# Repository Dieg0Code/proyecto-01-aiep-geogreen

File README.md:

# GeoGreen Escolar

GeoGreen comenzó como una propuesta para monitorear el llenado de contenedores de
reciclaje y evolucionó hacia un programa educativo de AIEP Osorno. El dispositivo
funciona como caso central para enseñar sostenibilidad, sensores, datos,
prototipado, desarrollo agéntico y comunicación de soluciones.

- **Socio comunitario:** Instituto Comercial Liceo Bicentenario, Osorno.
- **Público objetivo:** cerca de 60 estudiantes, organizados en equipos.
- **Programa:** tres talleres, cuatro mentorías, ensayo y competencia final.
- **Lógica tecnológica:** `sensar → enviar → visualizar → alertar`.

## Estado vigente · julio de 2026

El repositorio reúne dos líneas de trabajo conectadas:

1. **El dispositivo:** firmware, simulación, prototipos físicos, visualización,
   diseño 3D y PCB.
2. **El programa educativo:** talleres, cronograma, presentaciones, infografías,
   banco de ideas, inventario y materiales para la competencia.

Los Talleres 1 y 2 cuentan con planificación y presentación. El Taller 3 dispone
de un paquete completo de 90 minutos: README pedagógico, deck editable, banco
audiovisual, podcast de coordinación y una serie de cuatro infografías.

El calendario operativo vigente está centralizado en
[`cronograma/README.md`](cronograma/README.md). Los talleres se realizarán el 17,
18 y 24 de agosto; las mentorías se extenderán hasta el 28 de septiembre; el
evento final con jurado y premiación está programado para el 5 de octubre; y el
cierre interno corresponde a la semana del 12 de octubre.

## Evolución del dispositivo

GeoGreen no corresponde a un único circuito inmutable. El repositorio conserva
distintas versiones porque cada una responde a una etapa del proceso.

| Versión o track | Propósito | Estado |
|---|---|---|
| Prototipo original de referencia | `HC-SR04` + módulo de comunicación celular. No incluía semáforo ni buzzer. | Antecedente histórico reconstruido para explicar la evolución. |
| `arduino/` | Firmware base con porcentaje, semáforo y buzzer; simulación y pruebas con PlatformIO + Wokwi CLI. | Implementado y automatizado. |
| `arduino-r4/` | Prototipo físico con UNO R4 WiFi, `HC-SR04`, OLED, semáforo y buzzer; además, demos en la matriz LED integrada. | Construido y probado en protoboard. |
| `geogreen-v0/` | Validación de medición con ESP32 DevKit + sensor ultrasónico impermeable `A02YYUW`. | Track experimental de medición. |
| `geogreen-v1/` | PCB interna de dos capas con ESP32-C6, USB-C, conectores, semáforo y buzzer. | Candidata de diseño con DRC limpio; requiere revisión de ingeniería antes de fabricar. |
| `app/` | PWA con mapa de Osorno, estados, historial, batería, señal y alertas. | Interfaz funcional sobre una capa de telemetría reemplazable. |
| `web/` | Contenedor 3D interactivo y plano explosionado del módulo. | Demos funcionales sin proceso de build. |

La versión física educativa utilizada como demostración transforma una medición
de distancia en una respuesta comprensible:

1. El `HC-SR04` mide la distancia entre la tapa y el contenido.
2. La placa calcula un porcentaje de llenado.
3. El semáforo utiliza los umbrales `< 40 %`, `40–79 %` y `≥ 80 %`.
4. La OLED muestra porcentaje y estado.
5. El buzzer se activa en el estado rojo.
6. Una versión conectada puede enviar el dato para visualizarlo y generar alertas.

## Programa educativo y competencia

| Etapa | Fecha | Propósito |
|---|---|---|
| Taller 1 | Lunes 17 de agosto | Identificar un problema ambiental concreto y formar los equipos. |
| Taller 2 | Martes 18 de agosto | Comprender residuos, materiales, separación y reciclabilidad. |
| Taller 3 | Lunes 24 de agosto | Relacionar el problema con una variable, un sensor y una primera prueba segura. |
| Mentorías 1–4 | 31 de agosto al 28 de septiembre | Revisar avances, orientar decisiones y destrabar dificultades. |
| Evento final | Lunes 5 de octubre | Presentar ante el jurado, recibir retroalimentación y participar en la premiación. |

El desarrollo de las propuestas ocurre principalmente mediante el trabajo
autónomo de cada equipo entre sesiones. Las mentorías no sustituyen ese trabajo:
sirven para revisar evidencia, orientar y ayudar a resolver bloqueos concretos.

GeoGreen muestra hasta dónde puede crecer una idea, pero no es una solución que
los equipos deban copiar. La competencia valora la relación entre problema,
sensor, respuesta, evidencia, mejora y claridad de la presentación.

Los lineamientos comunes de participación, presentación, jurado, evaluación,
desempate y seguridad se encuentran en
[`concurso/README.md`](concurso/README.md). La versión institucional para
distribución está disponible en
[`concurso/documentos/lineamientos-concurso-final-geogreen.pdf`](concurso/documentos/lineamientos-concurso-final-geogreen.pdf).

## Inicio rápido

### Simulación y pruebas del firmware base

Requiere PlatformIO, Wokwi CLI y un token de Wokwi guardado fuera del repositorio
en `~/.wokwi_token`.

```bash
bash arduino/sim.sh
bash arduino/test.sh
```

### Prototipo físico UNO R4 WiFi

```bash
pio run -d arduino-r4/geogreen_proto
pio run -d arduino-r4/geogreen_proto -t upload
```

### Aplicación de monitoreo

```bash
cd app
npm install
npm run dev
```

### Visualización 3D

```bash
python -m http.server 8099 --directory web
```

Abrir `http://localhost:8099/` para el contenedor o
`http://localhost:8099/plano.html` para el plano del módulo.

## Mapa del repositorio

```text
.
├── arduino/                 # Firmware base, Wokwi, pruebas, cableado y 3D
├── arduino-r4/              # Demos y prototipo físico UNO R4 WiFi
├── geogreen-v0/             # Validación ESP32 DevKit + A02YYUW
├── geogreen-v1/             # PCB interna con ESP32-C6
├── app/                     # PWA de monitoreo
├── web/                     # Contenedor 3D y plano interactivo
├── talleres/01-03/          # Paquetes pedagógicos de los talleres
├── banco-ideas/             # Ideas semilla y sensores seleccionados
├── concurso/                # Lineamientos y documentos del evento final
├── cronograma/              # Calendario operativo vigente
├── reuniones/               # Materiales y antecedentes de coordinación
├── docs/                    # Inventario, infografías, presupuestos y guías
└── tools/                   # Sistema de slides y validadores
```

Índice ampliado de materiales: [`MATERIALES.md`](MATERIALES.md).

## Seguridad eléctrica esencial

- La UNO R4 WiFi trabaja con lógica de `5 V`; el pin `Echo` del `HC-SR04` puede
  conectarse directamente.
- Un ESP32 DevKit trabaja normalmente con lógica de `3,3 V`; el mismo `Echo` de
  `5 V` requiere divisor de voltaje o adaptación de nivel.
- Todo circuito se arma y revisa desconectado. Antes de energizar se comprueban
  voltaje, pinout, polaridad, resistencias y posibles cortocircuitos.

## Fuentes documentales

- [`RESUMEN-PROYECTO.md`](RESUMEN-PROYECTO.md) — alcance formal de la postulación y
  diferencia respecto del calendario operativo.
- [`PLAN-GEOGREEN-ESCOLAR.md`](PLAN-GEOGREEN-ESCOLAR.md) — estado de ejecución y
  articulación del programa.
- [`cronograma/documentos/cronograma-vigente-2026.md`](cronograma/documentos/cronograma-vigente-2026.md)
  — fuente única de fechas operativas.
- [`talleres/03/README.md`](talleres/03/README.md) — fuente pedagógica del Taller 3.
- [`concurso/README.md`](concurso/README.md) — lineamientos del Concurso Final
  GeoGreen Escolar 2026.

---

Proyecto académico de Vinculación con el Medio · AIEP Osorno · Ingeniería,
Energía y Tecnología + Desarrollo Social y Educación.

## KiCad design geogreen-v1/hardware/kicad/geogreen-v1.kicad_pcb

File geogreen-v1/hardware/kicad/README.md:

# GeoGreen V1 — PCB fab candidate (KiCad)

Placa V1 candidata a fabricacion: ruteada en 2 capas, sin ratsnest, con reporte
DRC limpio en KiCad 10 (`0 DRC violations`, `0 unconnected pads`). Sigue siendo
necesaria una revision humana de BOM/MPN/datasheets antes de ordenar unidades.

La placa se genera por script con la API Python de **KiCad 10** (`pcbnew`) y el
logo de serigrafía se vectoriza con **OpenCV**. Todos los componentes usan
footprints y modelos 3D estándar de KiCad, salvo el ESP32-C6 que usa el STEP
oficial de Espressif (con color).

## Cómo regenerar (orden)

Desde cualquier directorio (los scripts anclan sus rutas a su propia carpeta):

```bash
KDIR=geogreen-v1/hardware/kicad

# 1. Modelo 3D oficial del ESP32-C6.
#    Ya vive en models/ESP32-C6-MINI-1.step para que el render sea reproducible.
#    Fuente original: github.com/espressif/kicad-libraries

# 2. Logo AIEP -> poligonos de serigrafia (brand/logo_silk.json).
uv run --with opencv-python-headless --with numpy python "$KDIR/brand/vectorize_logo.py"

# 3. Generar la placa .kicad_pcb.
"/c/Program Files/KiCad/10.0/bin/python.exe" "$KDIR/create_v1_product_board.py"

# 4. Autorutear pistas 45°/ortogonales con Freerouting headless.
"/c/Program Files/KiCad/10.0/bin/python.exe" "$KDIR/autoroute.py"

# 5. Validar DRC.
kicad-cli pcb drc "$KDIR/geogreen-v1.kicad_pcb" --output "$KDIR/exports/drc.rpt"
```

Requisitos:
- `models/ESP32-C6-MINI-1.step` debe existir (paso 1) — es el módulo real con color.
- `brand/logo_silk.json` lo produce el paso 2 desde `brand/logo-aiep-source.png`.
- El root de footprints de KiCad se resuelve por la variable `KICAD10_FOOTPRINT_DIR`
  (o `KICAD_FOOTPRINT_DIR`), con fallback a la ruta por defecto de Windows.
- `autoroute.py` espera Java 25 en Scoop (`temurin-lts-jdk`) y Freerouting en
  `~/.local/lib/freerouting.jar`. Se puede sobrescribir con `GEOGREEN_JAVA` y
  `GEOGREEN_FREEROUTING_JAR`.

## Render 3D

Render fotorrealista (raytracing) — **usar `--quality high`**, no el `basic` por
defecto (que se ve gris/mate):

```bash
kicad-cli pcb render -o exports/geogreen-v1-product-render.jpg \
  --quality high --floor --perspective --width 1920 --height 1200 \
  --rotate '-25,0,-25' --background opaque geogreen-v1.kicad_pcb
```

## Fabricacion

```bash
kicad-cli pcb export gerbers geogreen-v1.kicad_pcb \
  --output exports/fabrication \
  --layers F.Cu,B.Cu,F.Paste,B.Paste,F.SilkS,B.SilkS,F.Mask,B.Mask,Edge.Cuts \
  --subtract-soldermask --check-zones

kicad-cli pcb export drill geogreen-v1.kicad_pcb \
  --output exports/fabrication --format excellon --excellon-units mm \
  --excellon-separate-th --generate-map --generate-report \
  --report-path exports/fabrication/drill-report.rpt

kicad-cli pcb export pos geogreen-v1.kicad_pcb \
  --output exports/fabrication/geogreen-v1-pos.csv \
  --format csv --units mm --side both
```

## Notas de diseño

- **Sensor ultrasónico A02YYUW**: es externo, impermeable (IP67), conectado por
  **cable con conector PH2.0-4P** (JST PH, paso 2.0 mm, 4 pines: VCC/GND/TX/RX).
  En la PCB solo va el header JST-PH que aparea con ese cable; el sensor no va
  montado en la placa y no se muestra en el render.
- Los designadores de referencia se ocultan en el render limpio; el archivo PCB
  mantiene referencias internas y la posicion de componentes se exporta en CSV.
- Algunos valores siguen siendo funcionales/genericos (`PTC`, `3V3_REG`) hasta
  cerrar BOM/MPN. No ordenar ensamble sin revisar esos MPN.
- El script genera zonas GND con hueco bajo la antena, pero no llama
  `ZONE_FILLER.Fill()` desde Python: KiCad 10 en Windows puede hacer crash con
  el footprint real `ESP32-C6-MINI-1` y ese keep-out. El autoruteo exporta DSN
  sin zonas para enrutar GND como pistas reales; los Gerbers se exportan con
  `--check-zones`.

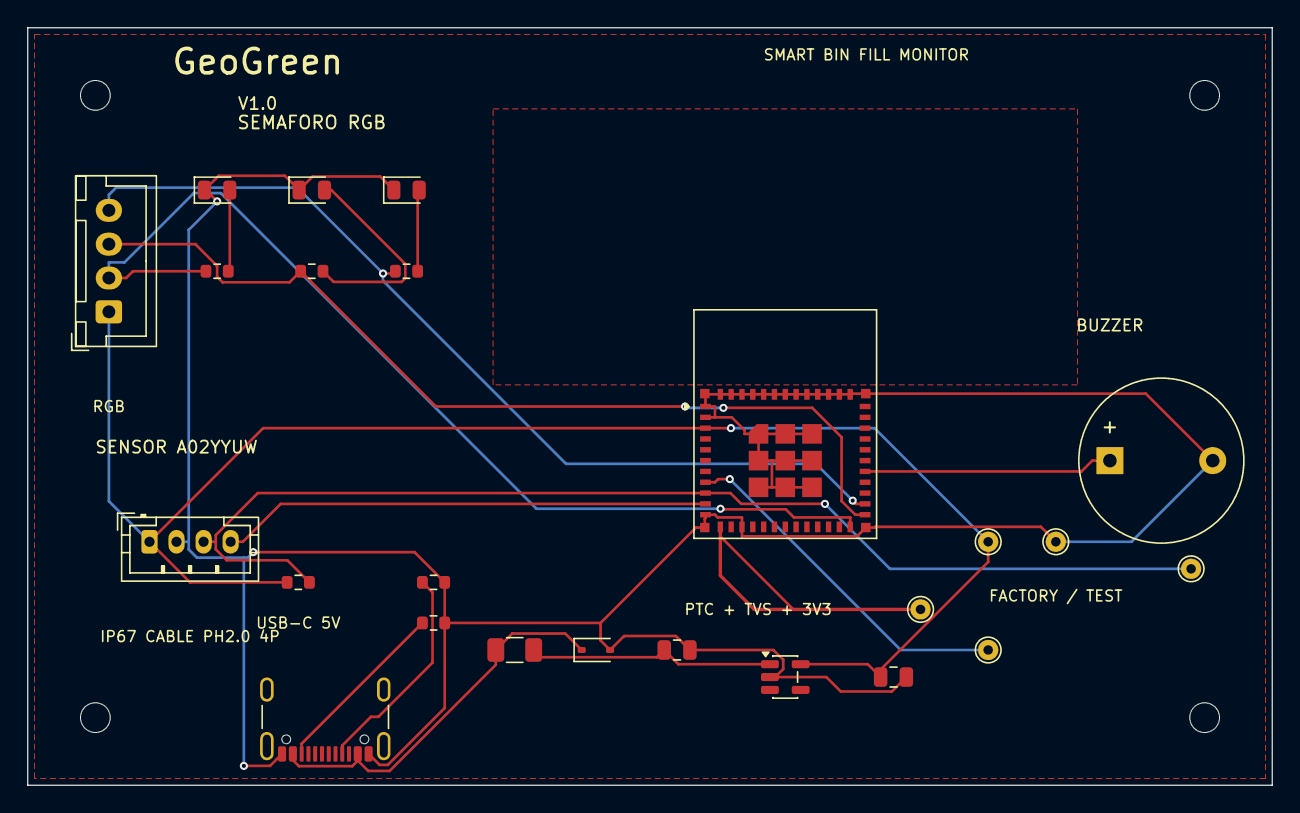
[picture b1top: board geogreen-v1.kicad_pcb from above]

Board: 2 copper layers, 92.0 x 56.0 mm, 28 parts (0 on the bottom side), 17 nets.

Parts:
BZ1: BUZZER; Buzzer_12x9.5RM7.6
C1, C2: 10uF; C_0805_2012Metric
D1: TVS; D_SOD-323
D2: LED_R; LED_0805_2012Metric
D3: LED_G; LED_0805_2012Metric
D4: LED_B; LED_0805_2012Metric
F1: PTC; Fuse_1206_3216Metric
H1, H2, H3, H4: M2; MountingHole_2.2mm_M2
J1: USB-C; USB_C_Receptacle_GCT_USB4105-xx-A_16P_TopMnt_Horizontal
J2: A02YYUW_PH2.0; JST_PH_B4B-PH-K_1x04_P2.00mm_Vertical
J4: RGB_SEMAFORO; JST_XH_B4B-XH-A_1x04_P2.50mm_Vertical
R1: CC1_5K1; R_0603_1608Metric
R2: CC2_5K1; R_0603_1608Metric
R3: SENSOR_RX_10K; R_0603_1608Metric
R4: LED_R_1K; R_0603_1608Metric
R5: LED_G_1K; R_0603_1608Metric
R6: LED_B_1K; R_0603_1608Metric
TP1: 3V3; TestPoint_THTPad_D1.5mm_Drill0.7mm
TP2: GND; TestPoint_THTPad_D1.5mm_Drill0.7mm
TP3: UART_RX; TestPoint_THTPad_D1.5mm_Drill0.7mm
TP4: EN; TestPoint_THTPad_D1.5mm_Drill0.7mm
TP5: BOOT; TestPoint_THTPad_D1.5mm_Drill0.7mm
U1: ESP32-C6-MINI-1
U2: 3V3_REG; SOT-23-5

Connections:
3V3: C2.1, J2.1, J4.1, R3.1, TP1.1, U1.3, U2.5
5V_PROTECTED: C1.1, F1.2, U2.1
BOOT_IO0: TP5.1, U1.12
BUZZER_OUT: BZ1.1, U1.29
EN: TP4.1, U1.8
GND: BZ1.2, C1.2, C2.2, D1.2, D2.1, D3.1, D4.1, J1.A1, J1.A12, J1.B1, J1.B12, J2.2, R1.2, R2.2, TP2.1, U1.1, U1.2, U1.11, U1.14, U1.36, U1.37, U1.38, U1.39, U1.40, U1.41, U1.42, U1.43, U1.44, U1.45, U1.46, U1.47, U1.48, U1.49, U1.50, U1.51, U1.52, U1.53, U2.2
LED_B: J4.4, R6.1, U1.26
LED_B_ANODE: D4.2, R6.2
LED_G: J4.3, R5.1, U1.25
LED_G_ANODE: D3.2, R5.2
LED_R: J4.2, R4.1, U1.24
LED_R_ANODE: D2.2, R4.2
SENSOR_RX_PULLUP: J2.4, U1.10
SENSOR_UART_RX: J2.3, R3.2, TP3.1, U1.9
USB_CC1: J1.A5, R1.1
USB_CC2: J1.B5, R2.1
VBUS_USB: D1.1, F1.1, J1.A4, J1.A9, J1.B4, J1.B9

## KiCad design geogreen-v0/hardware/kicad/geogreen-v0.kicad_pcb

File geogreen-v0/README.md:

# GeoGreen V0.1

Repositorio experimental de hardware y firmware para validar si un sensor
ultrasonico A02YYUW / SEN0311, montado bajo la tapa de un basurero, permite
clasificar de forma estable tres estados:

- `EMPTY`
- `MEDIUM`
- `FULL`

V0.1 no es el producto final. Es una prueba de medicion: sensor, lectura UART,
filtrado, calibracion y registro CSV por monitor serie.

El planteamiento inicial de la etapa posterior se conserva en
[`docs/v1-roadmap.md`](docs/v1-roadmap.md). Su implementación actual vive en
[`../geogreen-v1/`](../geogreen-v1/): PCB interna con ESP32-C6, USB-C, conector
de sensor, semáforo, buzzer y protección de energía.

## Arquitectura

```text
A02YYUW / SEN0311
  UART TX 9600 8N1
      |
      v
ESP32 Serial2 RX GPIO16
      |
      v
parser 4 bytes: 0xFF DATA_H DATA_L CHECKSUM
      |
      v
mediana ultimas 7 lecturas validas
      |
      v
fill_pct por calibracion EMPTY_DISTANCE_MM / FULL_DISTANCE_MM
      |
      v
CSV por USB Serial
```

Salida CSV:

```csv
timestamp_ms,raw_mm,filtered_mm,fill_pct,state,valid
```

## Alcance V0.1

Incluye:

- Lectura UART por `Serial2`.
- Validacion de header y checksum.
- Rechazo de frames invalidos.
- Mediana de las ultimas 7 lecturas validas.
- Calculo de porcentaje de llenado.
- Clasificacion `EMPTY`, `MEDIUM`, `FULL`.
- Documentacion base para futura PCB carrier de dos capas.

No incluye:

- Wi-Fi.
- Bluetooth.
- Backend.
- LEDs.
- Buzzer.
- Pantalla.
- PCB final.
- Footprint final del ESP32 DevKit.

## Carpetas

```text
geogreen-v0/
├── README.md
├── docs/
│   ├── requirements.md
│   ├── pinout.md
│   ├── test-plan.md
│   ├── measurements-format.md
│   └── v1-roadmap.md
├── firmware/
│   ├── geogreen_v0.ino
│   └── parser_tests.md
├── hardware/
│   ├── kicad-v0-checklist.md
│   └── schematic-plan.md
└── data/
    └── .gitkeep
```

## Flujo de trabajo recomendado

1. Confirmar modelo fisico exacto del ESP32 DevKit.
2. Confirmar distancia vacio/lleno del basurero real.
3. Cargar `firmware/geogreen_v0.ino` desde Arduino IDE.
4. Registrar CSV en `data/` durante pruebas controladas.
5. Evaluar estabilidad de `EMPTY`, `MEDIUM`, `FULL`.
6. Recien despues cerrar medidas para KiCad y una PCB fabricable.

## Riesgos de medicion

- El A02YYUW entrega distancia estable con RX alto, pero la estabilidad real bajo
  tapa depende del angulo, superficie del residuo y rebotes internos del basurero.
- La clasificacion puede oscilar cerca de los cortes si las distancias de
  calibracion quedan demasiado cerca.
- Residuos blandos, inclinados o con superficies irregulares pueden reflejar mal
  el ultrasonido.
- El montaje bajo tapa debe evitar que el sensor apunte a paredes laterales o
  bordes del contenedor.
- Alimentar el sensor a 3.3 V es parte de esta prueba; falta confirmar desempeno
  real frente a alimentacion nominal indicada por proveedor.

## Abrir el proyecto preliminar en KiCad

1. Abrir KiCad.
2. Abrir `geogreen-v0/hardware/kicad/geogreen-v0.kicad_pro`.
3. Revisar el PCB carrier y el reporte `hardware/kicad/exports/drc.rpt`.
4. Tratar el footprint ESP32 DevKit de 30 pines como referencia visual, no como
   una huella confirmada para fabricación.
5. Completar `hardware/kicad-v0-checklist.md` antes de cerrar medidas o conectores.

## KiCad CLI

En esta maquina `kicad-cli` esta instalado en:

```powershell
& "C:\Program Files\KiCad\10.0\bin\kicad-cli.exe" version
```

Exportaciones disponibles desde la CLI:

```powershell
& "C:\Program Files\KiCad\10.0\bin\kicad-cli.exe" sch export pdf geogreen-v0\hardware\kicad\geogreen-v0.kicad_sch -o geogreen-v0\hardware\kicad\exports\schematic.pdf
& "C:\Program Files\KiCad\10.0\bin\kicad-cli.exe" pcb export pdf geogreen-v0\hardware\kicad\geogreen-v0.kicad_pcb -o geogreen-v0\hardware\kicad\exports\pcb.pdf
```

El repositorio incluye un PCB preliminar en
`geogreen-v0/hardware/kicad/geogreen-v0.kicad_pcb`. Sirve para abrir en KiCad,
mirar 3D y exportar STEP para conversar carcasa. No es fabricable todavia: el
footprint del ESP32 DevKit es una referencia visual de 30 pines.

Artefactos ya exportados:

- Render: `hardware/kicad/exports/geogreen-v0-render.jpg`
- STEP para carcasa: `hardware/kicad/exports/geogreen-v0-carrier.step`
- DRC: `hardware/kicad/exports/drc.rpt`

El DRC actual no tiene cortos ni pads desconectados; quedan advertencias de
serigrafia por ser un layout preliminar.

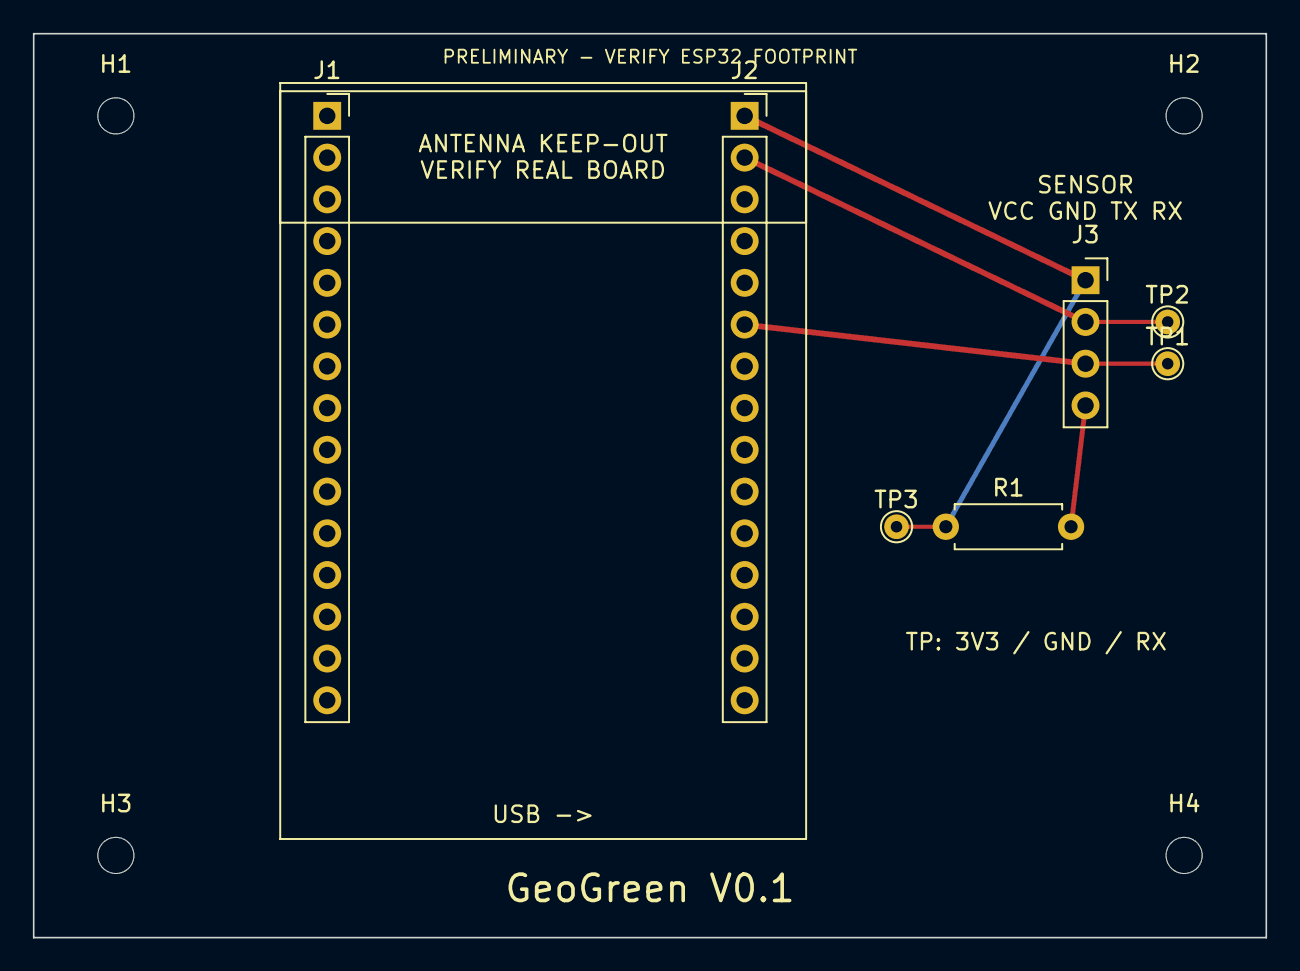
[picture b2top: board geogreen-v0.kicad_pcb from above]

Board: 2 copper layers, 75.0 x 55.0 mm, 11 parts (0 on the bottom side), 4 nets.

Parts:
H1, H2, H3, H4: M2; MountingHole_2.2mm_M2
J1: ESP32_LEFT_PROVISIONAL; PinSocket_1x15_P2.54mm_Vertical
J2: ESP32_RIGHT_PROVISIONAL; PinSocket_1x15_P2.54mm_Vertical
J3: A02YYUW_SENSOR; PinSocket_1x04_P2.54mm_Vertical
R1: 10k; R_Axial_DIN0207_L6.3mm_D2.5mm_P7.62mm_Horizontal
TP1: UART_RX; TestPoint_THTPad_D1.5mm_Drill0.7mm
TP2: GND; TestPoint_THTPad_D1.5mm_Drill0.7mm
TP3: 3V3; TestPoint_THTPad_D1.5mm_Drill0.7mm

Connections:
3V3: J2.1, J3.1, R1.1, TP3.1
GND: J2.2, J3.2, TP2.1
SENSOR_RX_PULLUP: J3.4, R1.2
UART_RX_GPIO16: J2.6, J3.3, TP1.1

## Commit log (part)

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2026-06-07 Add GeoGreen workshop coordination materials
2026-06-07 Add Codex agent guide
2026-06-08 add material de coordinacion y mejoras
2026-06-09 add material de coordinacion
2026-06-09 Add Taller 1 intro deck
2026-06-09 resumen formato podcast de lo planificado hasta el momento
2026-06-10 Finalize Taller 1 class deck
2026-06-10 Organize GeoGreen coordination materials
2026-06-14 Finalize Taller 2 GeoGreen deck
2026-06-15 Add GeoGreen coordination materials and meeting deck
2026-06-15 Refine meeting deck closing slide wording
2026-06-15 Polish coordination deck wording
2026-06-21 Update GeoGreen launch materials and schedule
2026-06-21 Add Taller 3 kits document
2026-06-21 Add GeoGreen physical prototype firmware for UNO R4
    Nuevo proyecto PlatformIO arduino-r4/geogreen_proto: HC-SR04 + semáforo de
    3 LEDs + buzzer + OLED I2C, con la lógica sensar->%->indicar->alertar.
    Filtrado del ruido del ultrasónico en varias capas: mediana de lecturas
    válidas, anti-saltos por confirmación (un eco falso lejano no tira el valor
    a 0), suavizado adaptativo, deadband del % e histéresis de color. Autotest
    de LEDs al arranque. Rango de escritorio para demo (vacío 25cm, lleno 3cm).
2026-06-21 Add Taller 3 progressive Arduino & sensors guide
    Guía LaTeX (tectonic) de cero a "tu propio sensor": protoboard, primer LED,
    semáforo, buzzer, lectura de sensor, integración medir->indicar->alertar,
    filtrado básico y método de 4 pasos para adaptar cualquier sensor del pool.
    Identidad visual AIEP; pensada como material del Taller 3.
2026-06-22 Scroll GeoGreen/AIEP brand on the R4 LED matrix in geogreen_proto
    Integra la marca del proyecto en la matriz LED integrada del UNO R4, de forma
    ASINCRONA (TextAnimation + play(), por interrupcion), para que el texto se
    desplace en bucle sin frenar el lazo del sensor/semaforo/buzzer/OLED.
2026-06-22 Add GeoGreen prototype build guide (pin map + wiring)
    Ficha de armado en LaTeX (tectonic) para rearmar o replicar el prototipo:
    mapa de pines exacto, esquema de conexion, notas de armado, comandos de
    flasheo y tabla de perillas de calibracion del firmware.
2026-06-22 Add socio-comunitario meeting podcast audio (Taller 3 sensors)
2026-06-22 Document geogreen_proto (physical prototype) in CLAUDE.md
    Marca geogreen_proto como el prototipo físico realizado (sensor + semáforo +
    buzzer + OLED + marca en matriz con filtrado robusto) y corrige el "no external
    parts" del track arduino-r4. Apunta a docs/armado-prototipo para el mapa de pines.
2026-06-22 Add working-prototype demo media (photo + video)
    Foto de la OLED mostrando 68% MEDIO con el LED amarillo encendido y un video
    del prototipo funcionando (sensor + semáforo + buzzer + pantalla), junto a la
    guía de armado.
2026-06-22 Add student 3D render of the prototype enclosure
    Render de la carcasa hecho por un estudiante del taller, comprimido de 83 MB a
    ~6 MB (H.264 CRF 24) para versionarlo liviano.
2026-06-22 Add 3D device-visualization slide with embedded video to launch deck
    Nueva slide "El dispositivo en 3D" (slide 10) en el deck del socio comunitario:
    render del modelo de la carcasa + video reproducible embebido. El video se
    incrusta tras la fusión con build/agregar-video.py (python-pptx add_movie),
    porque fusionar.py solo copia imágenes. El screencast de Blender se recortó
    para mostrar solo el modelo. Deck ahora 25 slides.
2026-06-22 Reword 3D slide bullet: enclosure design is AIEP's, not a liceo task
    "Los equipos modelan en 3D..." implicaba que los estudiantes del liceo diseñan
    la carcasa; es trabajo nuestro. Queda "El diseño 3D de la carcasa que protege
    el dispositivo" (descriptivo, sin atribuirlo al socio comunitario).
2026-06-22 Add Ley REP infographic and organize Taller 3 visuals
2026-06-22 Source and disambiguate slide 7 stats; fix moved infographic path
    Elías observó que las cifras del contexto Osorno eran ambiguas y sin fuente.
    Reetiquetadas según el grant: 25%→75% = cobertura de reciclaje domiciliario
    2025→2028 (Ley REP · ReSimple, antes "meta de reciclaje al 2028"), +1,3 M kg
    material recuperado en la comuna, +100 puntos limpios; agregada línea de fuentes
    (Municipalidad de Osorno · Ley 20.920 · convenio Osorno–ReSimple).
    Tambien corrige la ruta de IMG.proto en armar-geogreen.js: la infografia se movio
2026-06-30 add GeoGreen V0 hardware firmware track
